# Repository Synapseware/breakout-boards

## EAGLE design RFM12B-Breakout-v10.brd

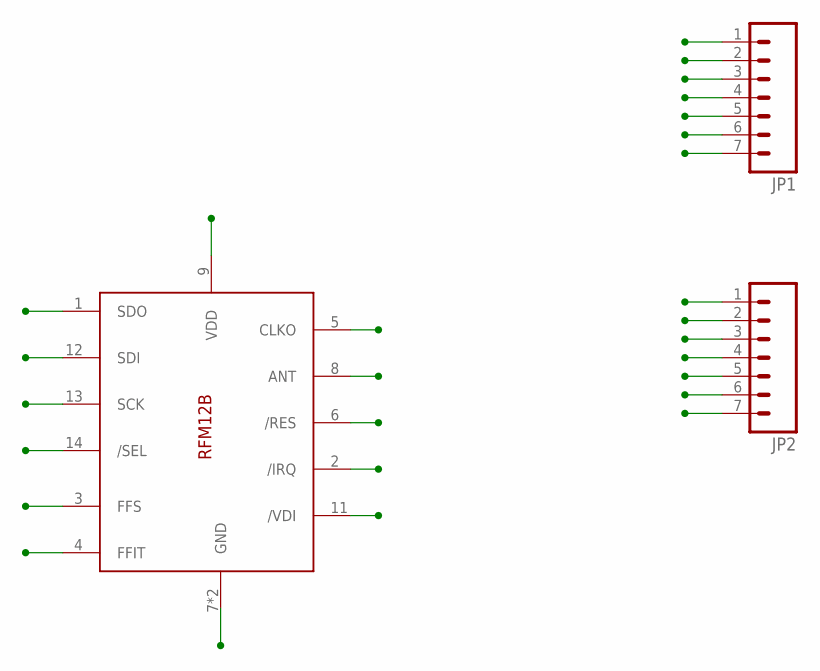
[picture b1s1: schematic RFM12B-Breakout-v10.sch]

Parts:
JP1, JP2: M07LONGPADS; 1X07_LONGPADS
U$1: RFM12B; RFM12B-MODULE

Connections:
ANT: JP2.7, U$1.8 (ANT)
CLKO: JP1.5, U$1.5 (CLKO)
FFIT: JP1.4, U$1.4 (FFIT)
FFS: JP1.3, U$1.3 (FFS)
GND: JP1.7, JP2.5, U$1.7 (GND), U$1.10 (GND)
IRQ: JP1.2, U$1.2 (/IRQ)
RES: JP1.6, U$1.6 (/RES)
SCK: JP2.2, U$1.13 (SCK)
SDI: JP2.3, U$1.12 (SDI)
SDO: JP1.1, U$1.1 (SDO)
SEL: JP2.1, U$1.14 (/SEL)
VDD: JP2.6, U$1.9 (VDD)
VDI: JP2.4, U$1.11 (/VDI)

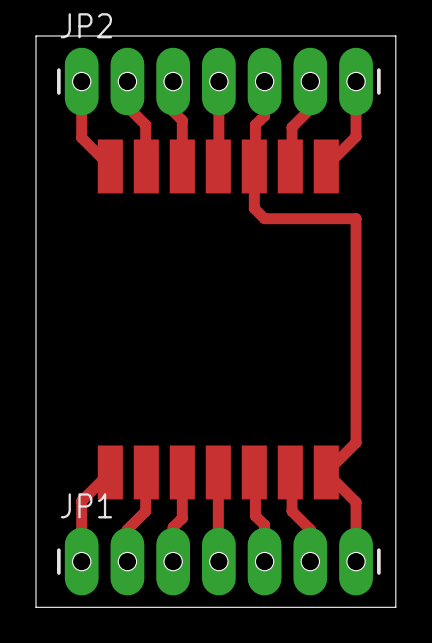
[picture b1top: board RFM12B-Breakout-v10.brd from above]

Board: 2 copper layers, 20.0 x 31.7 mm, 3 parts (0 on the bottom side), 13 nets.

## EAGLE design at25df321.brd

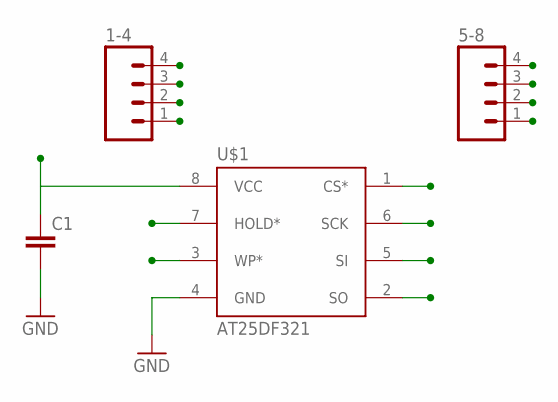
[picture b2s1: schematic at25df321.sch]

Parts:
1-4, 5-8: M04PTH; 1X04
C1: CAP1206; 1206
U$1: AT25DF321; WSOIC-8

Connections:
CS*: 1-4.1, U$1.1 (CS*)
GND: 1-4.4, C1.2, U$1.4 (GND)
HOLD*: 5-8.3, U$1.7 (HOLD*)
SCK: 5-8.2, U$1.6 (SCK)
SI: 5-8.1, U$1.5 (SI)
SO: 1-4.2, U$1.2 (SO)
VCC: 5-8.4, C1.1, U$1.8 (VCC)
WP*: 1-4.3, U$1.3 (WP*)

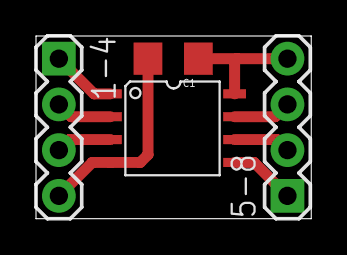
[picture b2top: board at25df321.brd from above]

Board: 2 copper layers, 15.3 x 10.2 mm, 4 parts (0 on the bottom side), 8 nets.

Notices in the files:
parts and their libraries:
SparkFun-Connectors: Licensing: CC v3.0 Share-Alike You are welcome to use this library for commercial purposes.
